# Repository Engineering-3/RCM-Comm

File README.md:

RCM-Comm
========================

This is an interface board that brings wireless communication to the RCM Control Stack. The RCM-Comm accepts the [Lantronix XPico WiFi Embedded Device Server](https://www.lantronix.com/wp-content/uploads/pdf/xPico-Wi-Fi_UG.pdf). Please see [Engineering3](http://engineering3.org/) for more information on the complete RCM Control Stack project.

Repository Contents
-------------------

* **/RCM-Comm_v1** Eagle schematic/board files, BOM, gerbers

Version History
---------------
* [RCM-Comm_v1](https://github.com/Engineering-3/RCM-Comm/tree/master/RCM-Comm_v1) - First public version - version 1 

License Information
-------------------
Hardware is released under [Solderpad Hardware License v0.51](http://solderpad.org/licenses/SHL-0.51/).
Distributed as-is; no warranty is given.

Getting Started Help
--------------------
This is a Plug-n-Play board.

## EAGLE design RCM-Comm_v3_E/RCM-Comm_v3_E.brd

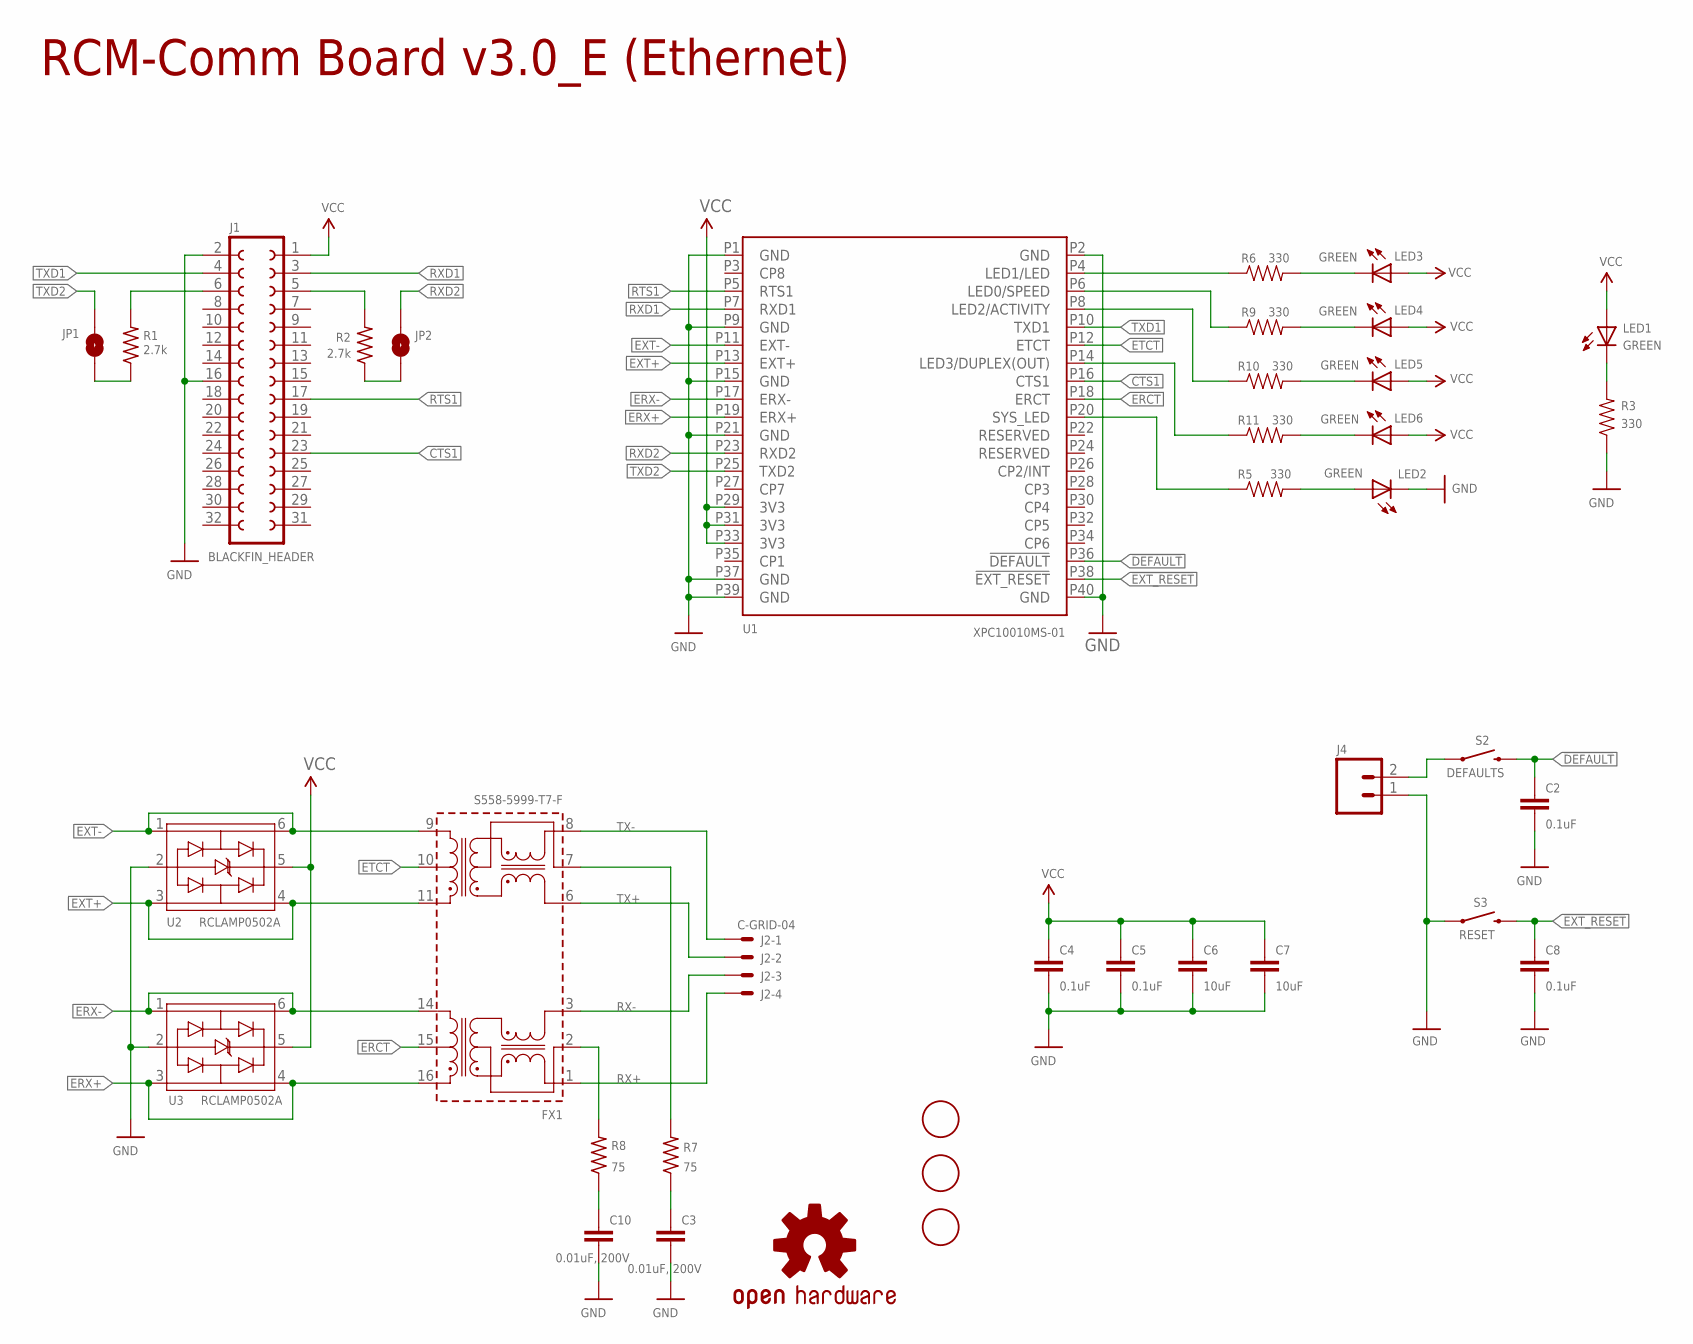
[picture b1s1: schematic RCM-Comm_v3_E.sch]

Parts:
C2, C4, C5, C8: 0.1uF; 0603-CAP
C3, C10: 0.01uF, 200V; 0603-CAP
C6, C7: 10uF; 0603-CAP
FID1, FID2, FID3: FIDUCIAL; FIDUCIAL_1MM
FX1: S558-5999-T7-F; N5
J1: BLACKFIN_HEADER; 2X16
J2-: C-GRID-04; 70555-04
J4: M02LOCK; 1X02_LOCK
JP1, JP2: JUMPER-PAD-2-NOROUND; PAD-JUMPER-2-NO_YES_SILK_ROUND
LED1, LED2, LED3, LED4, LED5, LED6: GREEN; LED-0603
LOGO1: OSHW-LOGOM; OSHW-LOGO-M
R1, R2: 2.7k; R0603
R3, R5, R6, R9, R10, R11: 330; 0603-RES
R7, R8: 75; R0603
S2: DEFAULTS; TACTILE-SWITCH-SMD
S3: RESET; TACTILE-SWITCH-SMD
U1: XPC10010MS-01; LANTRONIX_XPICO
U2, U3: RCLAMP0502A; SC-89
U$3: ROHS_GARBAGE; ROHS_GARBAGE_5MM

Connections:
!DEFAULT!: C2.1, S2.3 (2), U1.P36 (!DEFAULT!)
!EXT_RESET!: C8.1, S3.3 (2), U1.P38 (!EXT_RESET!)
CTS1: J1.23 (GP6), U1.P16 (CTS1)
ERCT: FX1.15, U1.P18 (ERCT)
ERX+: FX1.16, U1.P19 (ERX+), U3.3, U3.4
ERX-: FX1.14, U1.P17 (ERX-), U3.1, U3.6
ETCT: FX1.10, U1.P12 (ETCT)
EXT+: FX1.11, U1.P13 (EXT+), U2.3, U2.4
EXT-: FX1.9, U1.P11 (EXT-), U2.1, U2.6
GND: C2.2, C3.2, C4.2, C5.2, C6.2, C7.2, C8.2, C10.2, J1.2 (GND), J1.16 (GND16), J4.1, LED2.C, R3.1, S3.1, U1.P1 (GND), U1.P2 (GND), U1.P9 (GND), U1.P15 (GND), U1.P21 (GND), U1.P37 (GND), U1.P39 (GND), U1.P40 (GND), U2.2, U3.2
LED0_SPEED: R9.1, U1.P6 (LED0/SPEED)
LED1_LINK: R6.1, U1.P4 (LED1/LED)
LED2_ACTIVITY: R10.1, U1.P8 (LED2/ACTIVITY)
LED3_DUPLEX: R11.1, U1.P14 (LED3/DUPLEX(OUT))
unnamed: J4.2, S2.1
unnamed: JP1.2, R1.1
unnamed: LED1.C, R3.2
unnamed: JP2.1, R2.1
unnamed: LED2.A, R5.2
unnamed: FX1.2, R8.2
unnamed: LED3.C, R6.2
unnamed: C10.1, R8.1
unnamed: C3.1, R7.1
unnamed: FX1.7, R7.2
unnamed: LED6.C, R11.2
unnamed: LED5.C, R10.2
unnamed: LED4.C, R9.2
RTS1: J1.17 (GP0), U1.P5 (RTS1)
RX+: FX1.1, J2-.4
RX-: FX1.3, J2-.3
RXD1: J1.3 (TX0), U1.P7 (RXD1)
RXD2: JP2.2, U1.P23 (RXD2)
RXD2_J1: J1.5 (TX1), R2.2
SYSTEM_LED: R5.1, U1.P20 (SYS_LED)
TX+: FX1.6, J2-.2
TX-: FX1.8, J2-.1
TXD1: J1.4 (RX0), U1.P10 (TXD1)
TXD2: JP1.1, U1.P25 (TXD2)
TXD2_J1: J1.6 (RX1), R1.2
VCC: C4.1, C5.1, C6.1, C7.1, J1.1 (3.3V), LED1.A, LED3.A, LED4.A, LED5.A, LED6.A, U1.P29 (3V3), U1.P31 (3V3), U1.P33 (3V3), U2.5, U3.5

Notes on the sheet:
RCM-Comm Board v3.0_E (Ethernet)

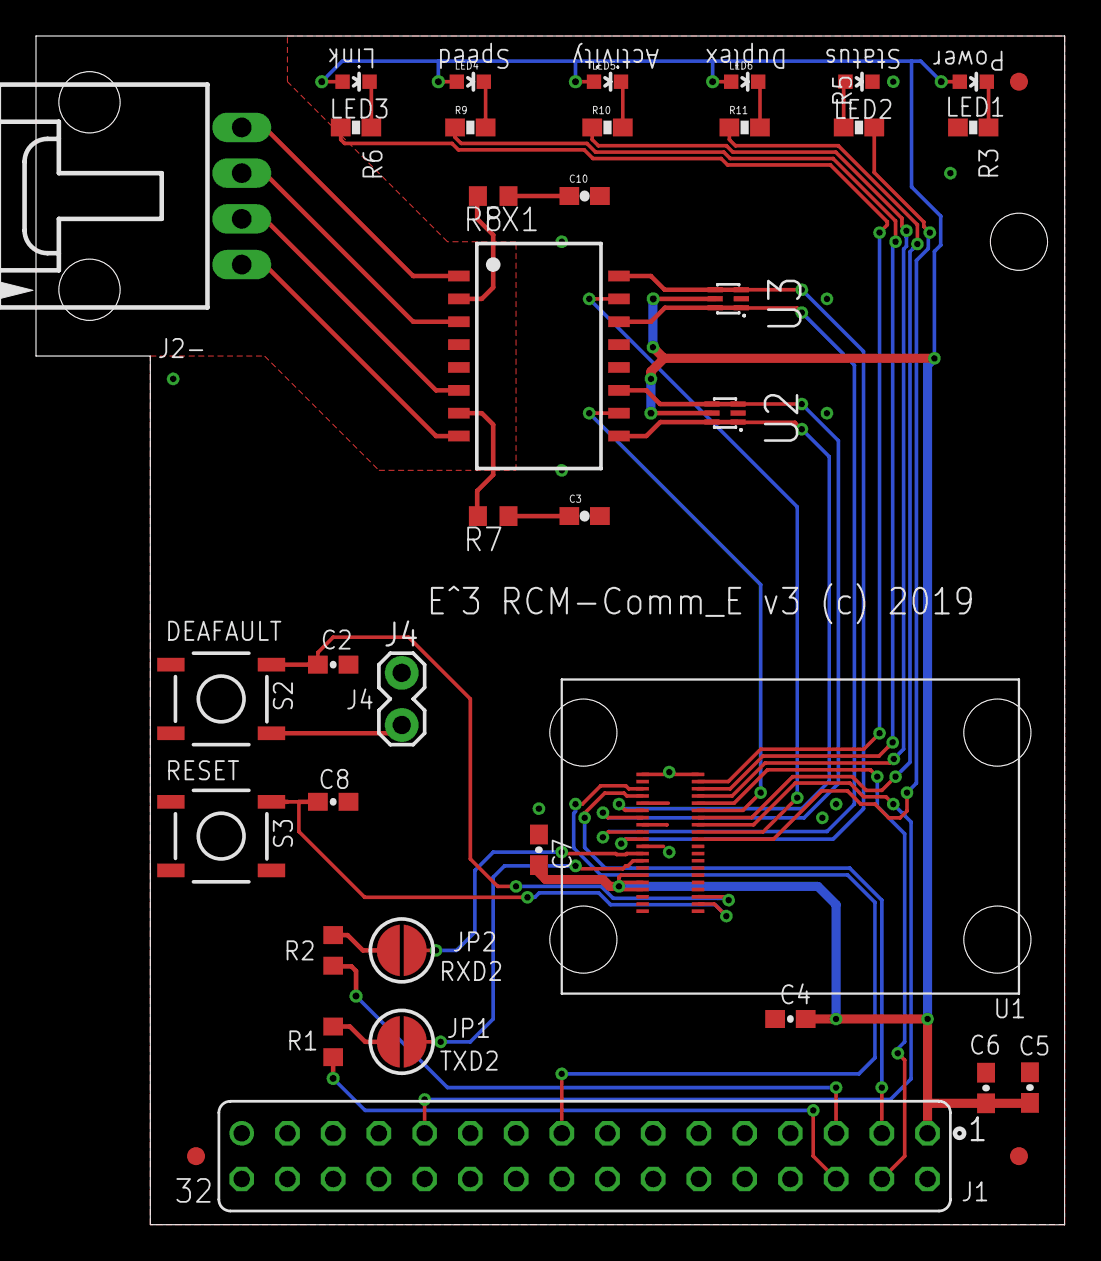
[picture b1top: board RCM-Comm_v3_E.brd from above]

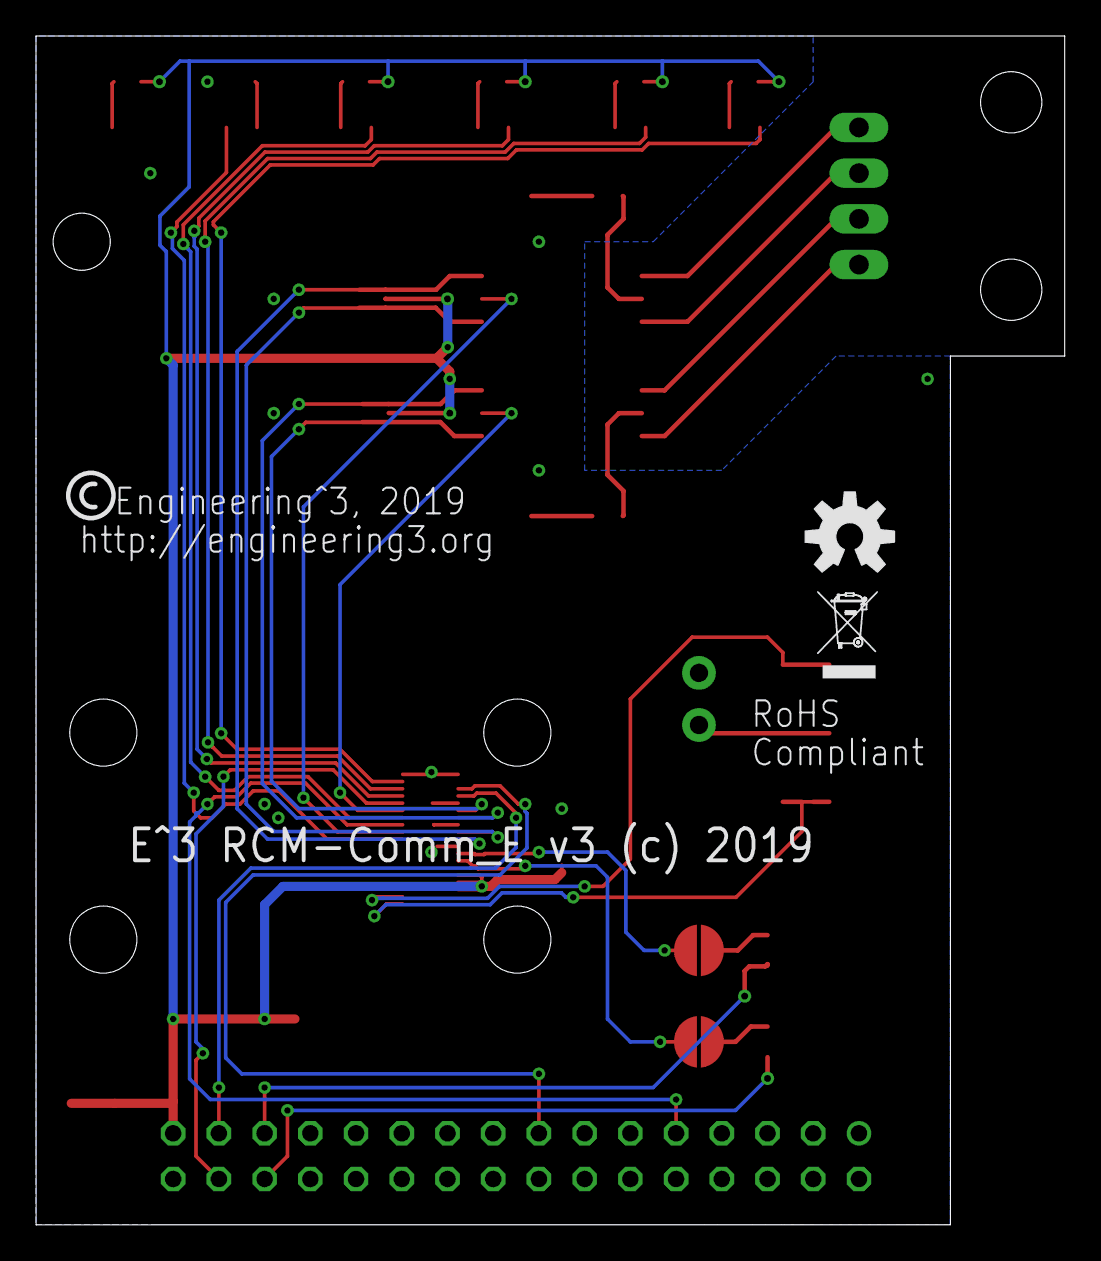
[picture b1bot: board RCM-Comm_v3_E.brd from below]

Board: 2 copper layers, 57.2 x 66.0 mm, 40 parts (2 on the bottom side), 40 nets.

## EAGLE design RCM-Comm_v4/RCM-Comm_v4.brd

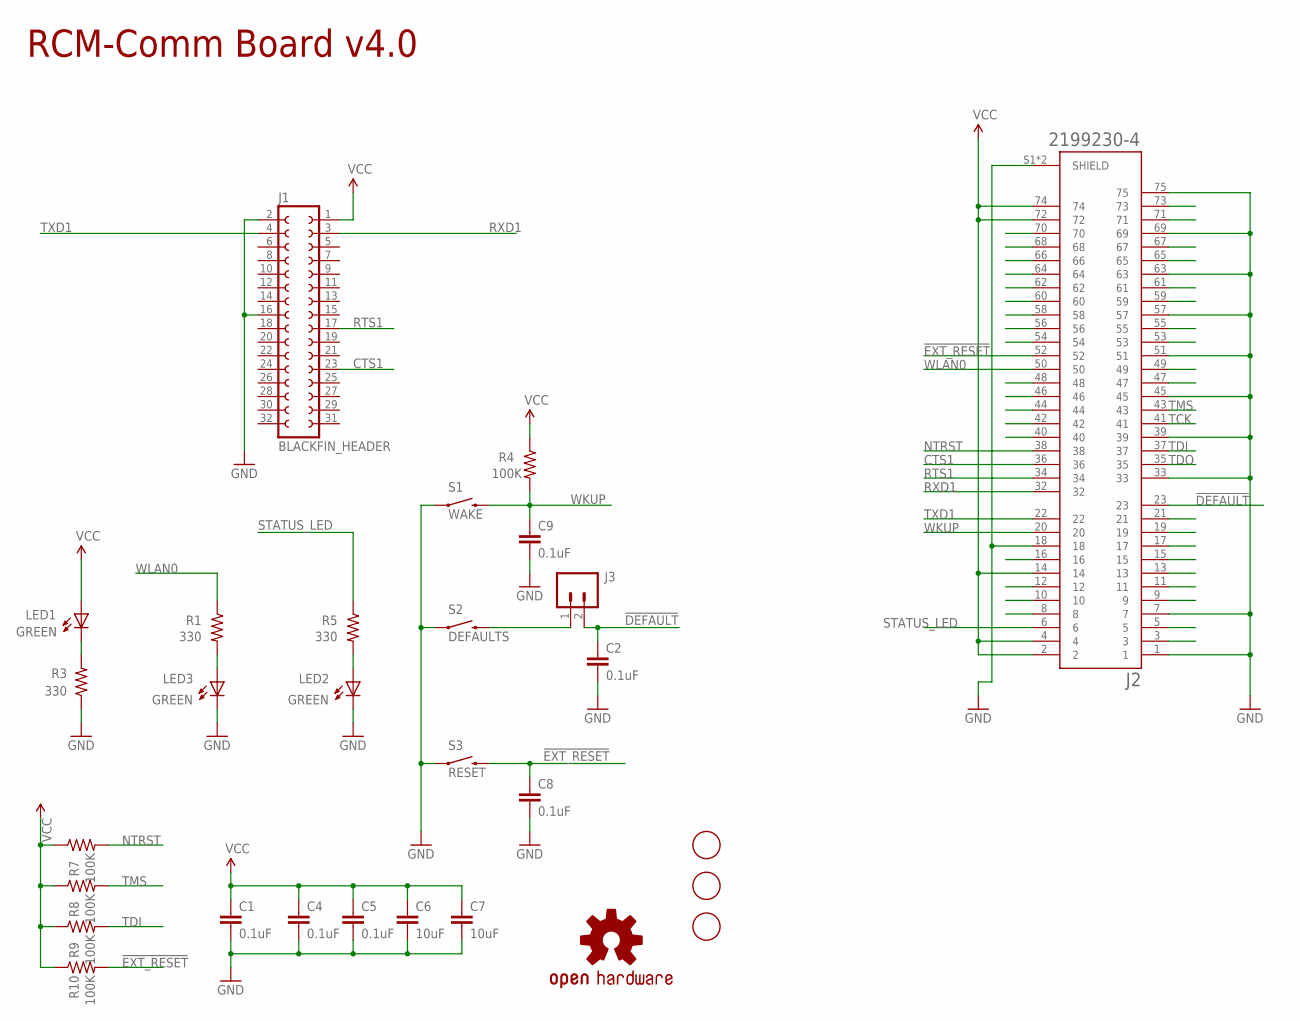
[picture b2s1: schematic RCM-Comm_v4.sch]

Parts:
C1, C2, C4, C5, C8, C9: 0.1uF; 0603-CAP
C6, C7: 10uF; 0603-CAP
FID1, FID2, FID3: FIDUCIAL; FIDUCIAL_1MM
J1: BLACKFIN_HEADER; 2X16
J2: 2199230-4; TE_2199230-4
J3: CONN_02; 1X02
LED1, LED2, LED3: GREEN; LED-0603
LOGO1: OSHW-LOGOM; OSHW-LOGO-M
R1, R3, R5: 330; 0603-RES
R4, R7, R8, R9, R10: 100K; 0603-RES
S1: WAKE; TACTILE-SWITCH-SMD
S2: DEFAULTS; TACTILE-SWITCH-SMD
S3: RESET; TACTILE-SWITCH-SMD
U$3: ROHS_GARBAGE; ROHS_GARBAGE_5MM

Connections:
!DEFAULT!: C2.1, J2.23, J3.2
!EXT_RESET!: C8.1, J2.52, R10.2, S3.3 (2)
CTS1: J1.23 (GP6), J2.36
GND: C1.2, C2.2, C4.2, C5.2, C6.2, C7.2, C8.2, C9.2, J1.2 (GND), J1.16 (GND16), J2.1, J2.7, J2.18, J2.33, J2.39, J2.45, J2.51, J2.57, J2.63, J2.69, J2.75, J2.S1 (SHIELD), J2.S2 (SHIELD), LED2.C, LED3.C, R3.1, S1.1, S2.1, S3.1
unnamed: J3.1, S2.3 (2)
unnamed: LED3.A, R1.2
unnamed: LED1.C, R3.2
unnamed: LED2.A, R5.2
NTRST: J2.38, R7.2
RTS1: J1.17 (GP0), J2.34
RXD1: J1.3 (TX0), J2.32
STATUS_LED: J2.6, R5.1
TCK: J2.41
TDI: J2.37, R9.2
TDO: J2.35
TMS: J2.43, R8.2
TXD1: J1.4 (RX0), J2.22
VCC: C1.1, C4.1, C5.1, C6.1, C7.1, J1.1 (3.3V), J2.2, J2.4, J2.14, J2.72, J2.74, LED1.A, R4.1, R7.1, R8.1, R9.1, R10.1
WKUP: C9.1, J2.20, R4.2, S1.3 (2)
WLAN0: J2.50, R1.1

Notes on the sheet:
RCM-Comm Board v4.0

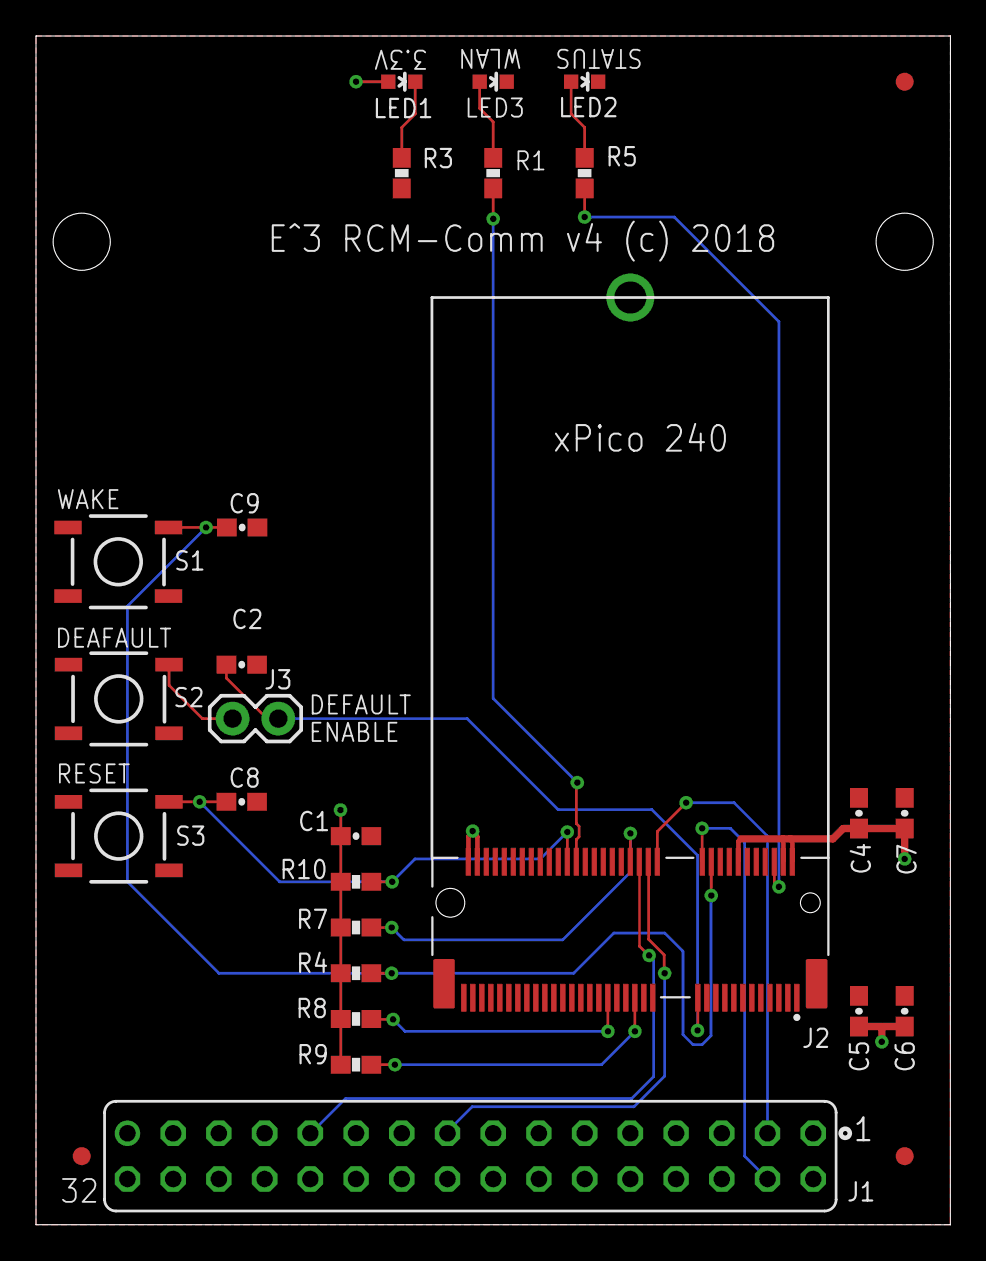
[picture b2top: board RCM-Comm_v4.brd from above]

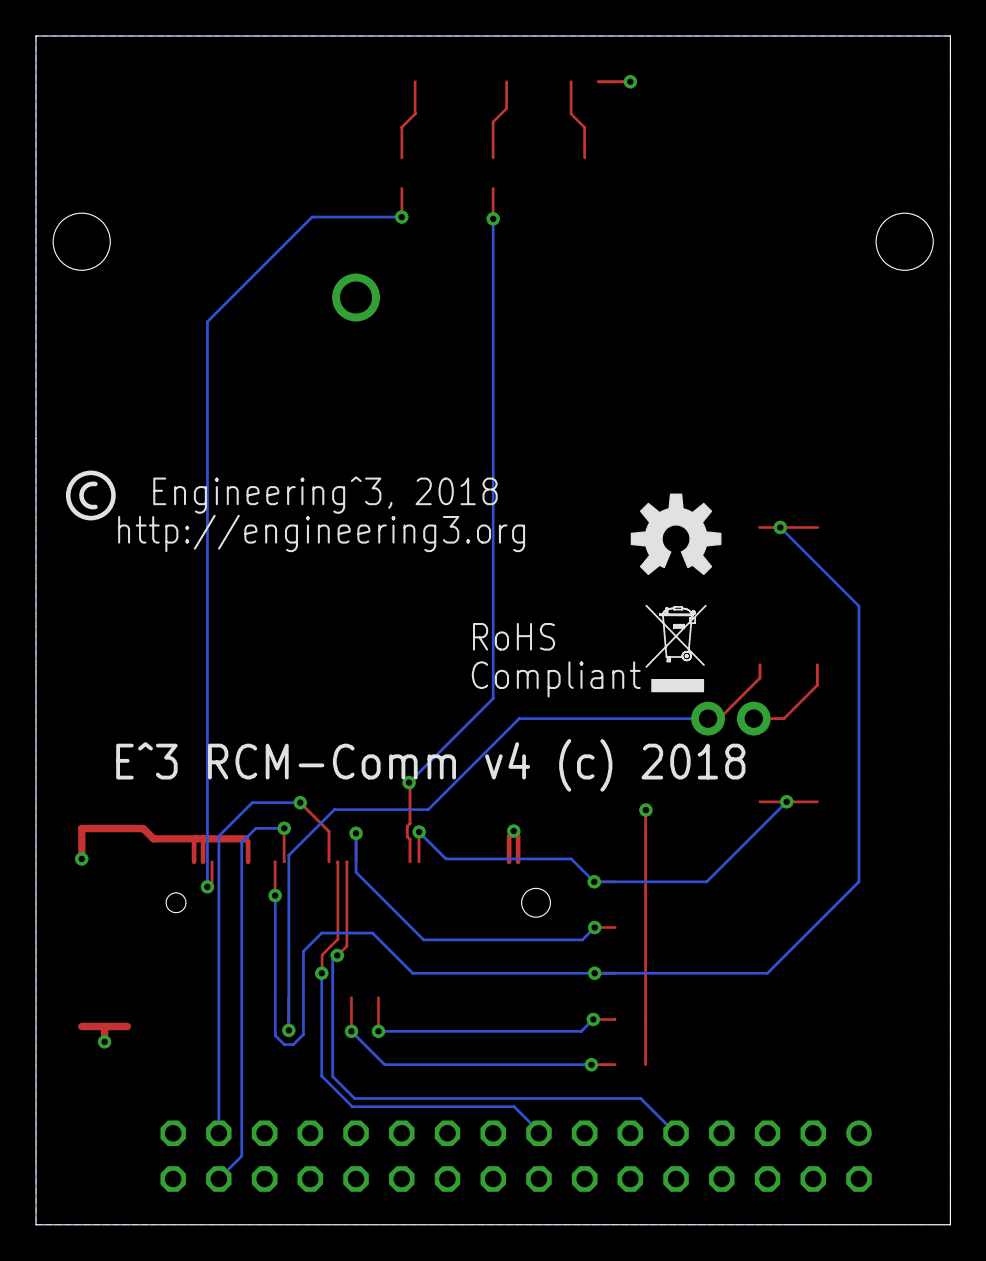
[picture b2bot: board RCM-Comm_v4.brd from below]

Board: 2 copper layers, 50.8 x 66.0 mm, 30 parts (2 on the bottom side), 18 nets.

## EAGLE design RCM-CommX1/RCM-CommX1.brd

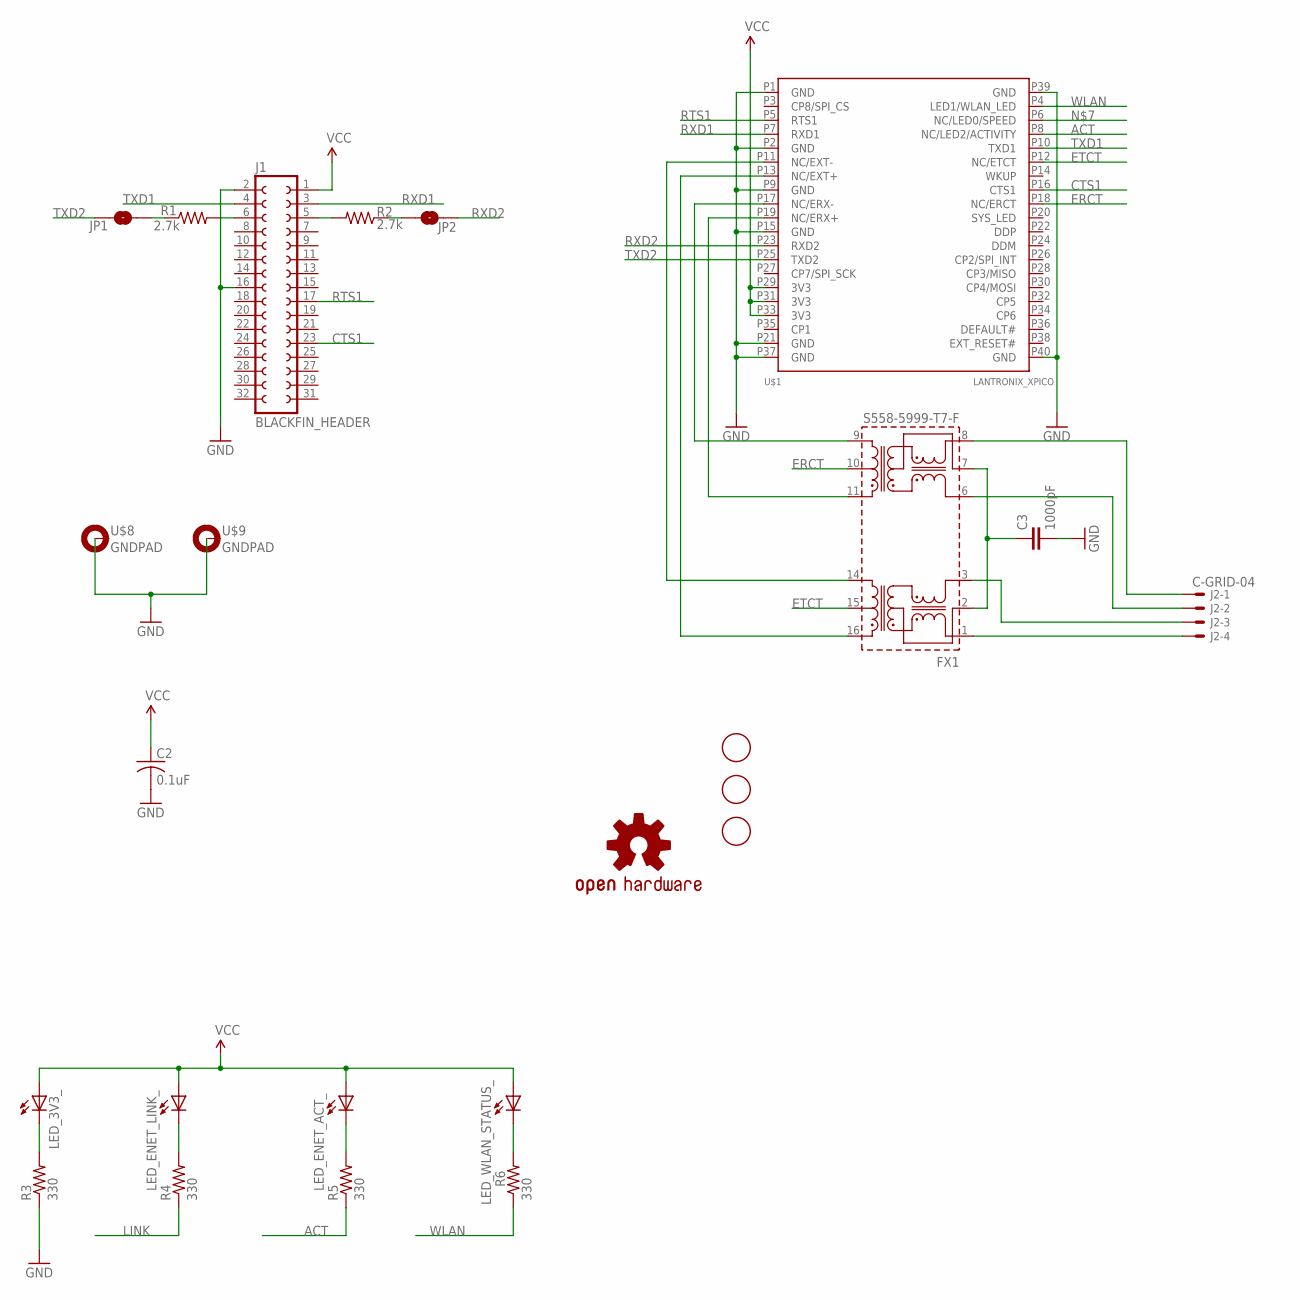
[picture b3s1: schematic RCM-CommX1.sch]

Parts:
C2: 0.1uF; C0603
C3: 1000pF; 0603-CAP
FID1, FID2, FID3: FIDUCIAL; FIDUCIAL_1MM
FX1: S558-5999-T7-F; N5
J1: BLACKFIN_HEADER; 2X16
J2-: C-GRID-04; 70555-04
JP1, JP2: JUMPER-PAD-2-NOROUND; PAD-JUMPER-2-NO_YES_SILK_ROUND
LED_3V3_: LED0603; LED-0603
LED_ENET_ACT_: LED0603; LED-0603
LED_ENET_LINK_: LED0603; LED-0603
LED_WLAN_STATUS_: LED0603; LED-0603
LOGO1: OSHW-LOGOM; OSHW-LOGO-M
R1, R2: 2.7k; R0603
R3, R4, R5, R6: 330; 0603-RES
U$1: LANTRONIX_XPICO
U$3: ROHS_GARBAGE; ROHS_GARBAGE_5MM
U$8, U$9: GNDPAD

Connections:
ACT: R5.1, U$1.P8 (NC/LED2/ACTIVITY)
CTS1: J1.23 (GP6), U$1.P16 (CTS1)
ERCT: FX1.10, U$1.P18 (NC/ERCT)
ETCT: FX1.15, U$1.P12 (NC/ETCT)
GND: C2.2, C3.2, J1.2 (GND), J1.16 (GND16), R3.1, U$1.P1 (GND), U$1.P2 (GND), U$1.P9 (GND), U$1.P15 (GND), U$1.P21 (GND), U$1.P37 (GND), U$1.P39 (GND), U$1.P40 (GND), U$8.P$1, U$9.P$1
LINK: R4.1
unnamed: C3.1, FX1.2, FX1.7
unnamed: JP1.2, R1.1
unnamed: LED_3V3_.C, R3.2
unnamed: JP2.1, R2.1
unnamed: LED_ENET_LINK_.C, R4.2
unnamed: LED_ENET_ACT_.C, R5.2
unnamed: LED_WLAN_STATUS_.C, R6.2
unnamed: FX1.16, U$1.P13 (NC/EXT+)
unnamed: FX1.14, U$1.P11 (NC/EXT-)
unnamed: FX1.11, U$1.P19 (NC/ERX+)
unnamed: FX1.9, U$1.P17 (NC/ERX-)
unnamed: FX1.1, J2-.4
unnamed: FX1.3, J2-.3
unnamed: FX1.8, J2-.1
unnamed: FX1.6, J2-.2
unnamed: J1.6 (RX1), R1.2
unnamed: J1.5 (TX1), R2.2
RTS1: J1.17 (GP0), U$1.P5 (RTS1)
RXD1: J1.3 (TX0), U$1.P7 (RXD1)
RXD2: JP2.2, U$1.P23 (RXD2)
TXD1: J1.4 (RX0), U$1.P10 (TXD1)
TXD2: JP1.1, U$1.P25 (TXD2)
VCC: C2.1, J1.1 (3.3V), LED_3V3_.A, LED_ENET_ACT_.A, LED_ENET_LINK_.A, LED_WLAN_STATUS_.A, U$1.P29 (3V3), U$1.P31 (3V3), U$1.P33 (3V3)
WLAN: R6.1, U$1.P4 (LED1/WLAN_LED)

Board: 2 copper layers, 25 parts (2 on the bottom side), 29 nets, no tracks yet.

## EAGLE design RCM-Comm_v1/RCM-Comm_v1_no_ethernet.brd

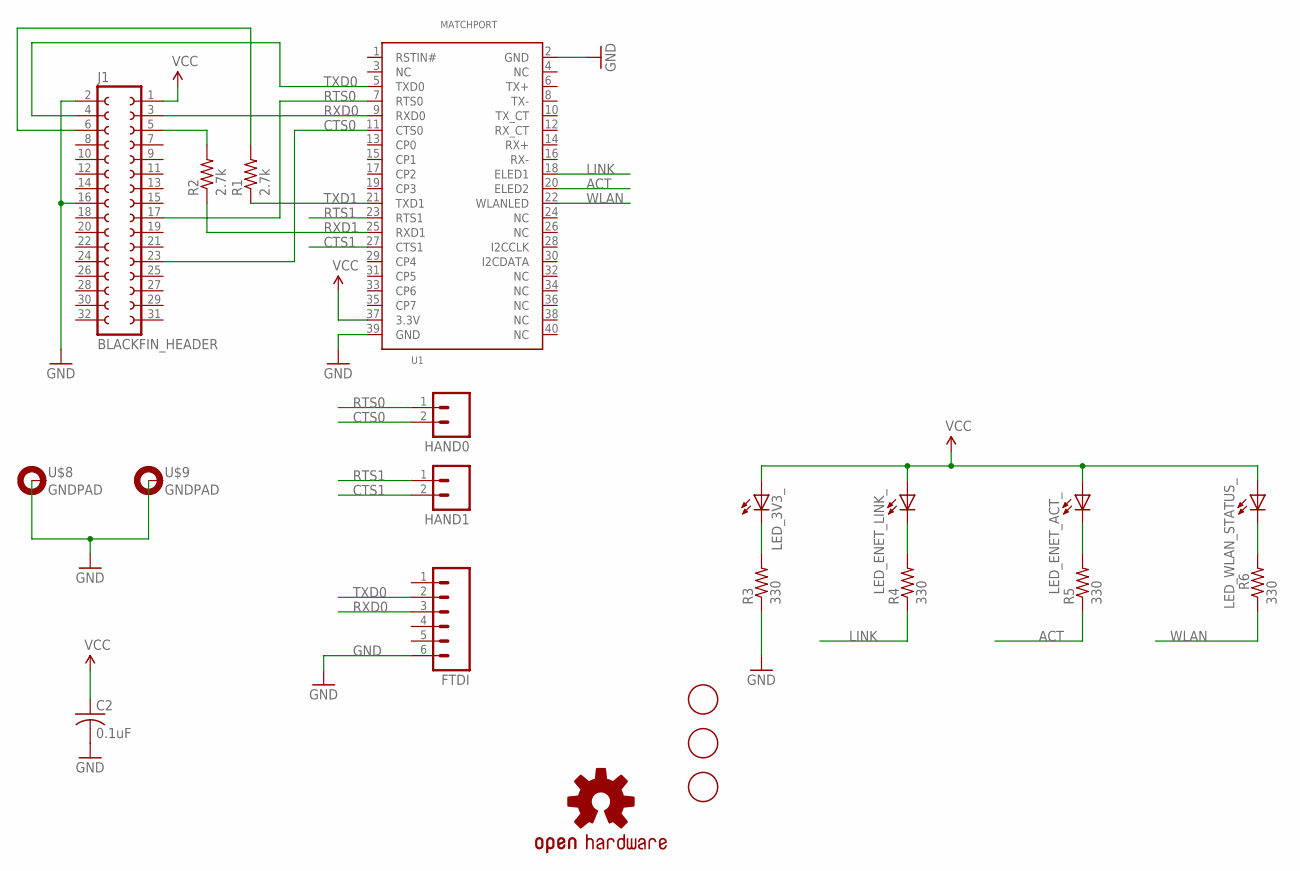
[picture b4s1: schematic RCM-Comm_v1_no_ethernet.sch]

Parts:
C2: 0.1uF; C0603
FID1, FID2, FID3: FIDUCIAL; FIDUCIAL_1MM
FTDI: M06SIP; 1X06
HAND0, HAND1: M02PTH; 1X02
J1: BLACKFIN_HEADER; 2X16
LED_3V3_: LED0603; LED-0603
LED_ENET_ACT_: LED0603; LED-0603
LED_ENET_LINK_: LED0603; LED-0603
LED_WLAN_STATUS_: LED0603; LED-0603
LOGO1: OSHW-LOGOM; OSHW-LOGO-M
R1, R2: 2.7k; 0207/10
R3, R4, R5, R6: 330; 0603-RES
U1: MATCHPORT; MATCHPORT_LAYOUT
U$3: ROHS_GARBAGE; ROHS_GARBAGE_5MM
U$8, U$9: GNDPAD

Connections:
ACT: R5.1, U1.20 (ELED2)
CTS0: HAND0.2, J1.23 (GP6), U1.11 (CTS0)
CTS1: HAND1.2, U1.27 (CTS1)
GND: C2.2, FTDI.6, J1.2 (GND), J1.16 (GND16), R3.1, U1.2 (GND), U1.39 (GND), U$8.P$1, U$9.P$1
LINK: R4.1, U1.18 (ELED1)
unnamed: LED_3V3_.C, R3.2
unnamed: LED_ENET_LINK_.C, R4.2
unnamed: LED_ENET_ACT_.C, R5.2
unnamed: LED_WLAN_STATUS_.C, R6.2
unnamed: J1.6 (RX1), R1.2
unnamed: J1.5 (TX1), R2.2
RTS0: HAND0.1, J1.17 (GP0), U1.7 (RTS0)
RTS1: HAND1.1, U1.23 (RTS1)
RXD0: FTDI.3, J1.3 (TX0), U1.9 (RXD0)
RXD1: R2.1, U1.25 (RXD1)
TXD0: FTDI.2, J1.4 (RX0), U1.5 (TXD0)
TXD1: R1.1, U1.21 (TXD1)
VCC: C2.1, J1.1 (3.3V), LED_3V3_.A, LED_ENET_ACT_.A, LED_ENET_LINK_.A, LED_WLAN_STATUS_.A, U1.37 (3.3V)
WLAN: R6.1, U1.22 (WLANLED)

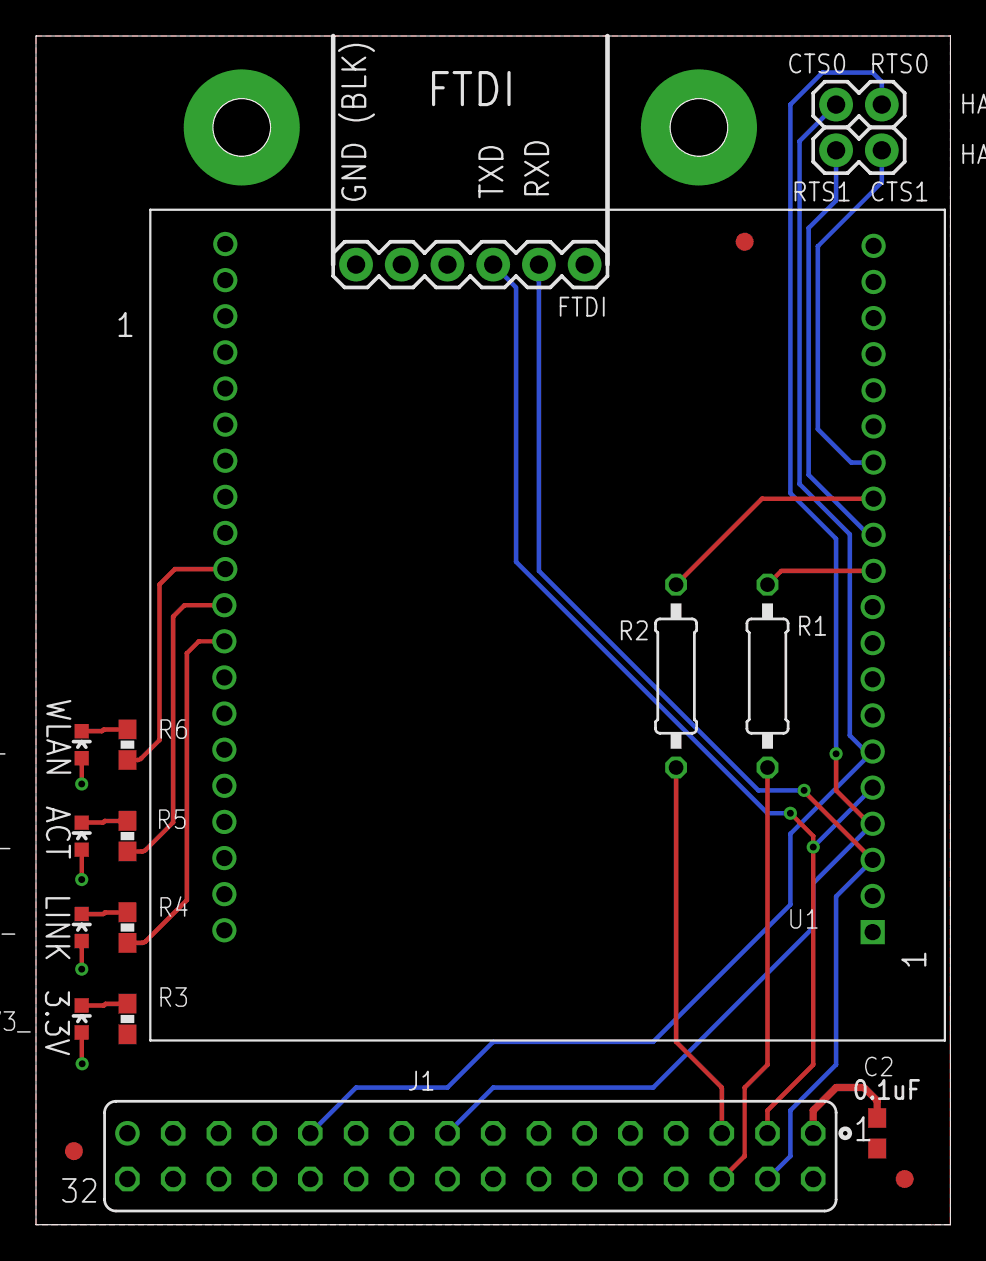
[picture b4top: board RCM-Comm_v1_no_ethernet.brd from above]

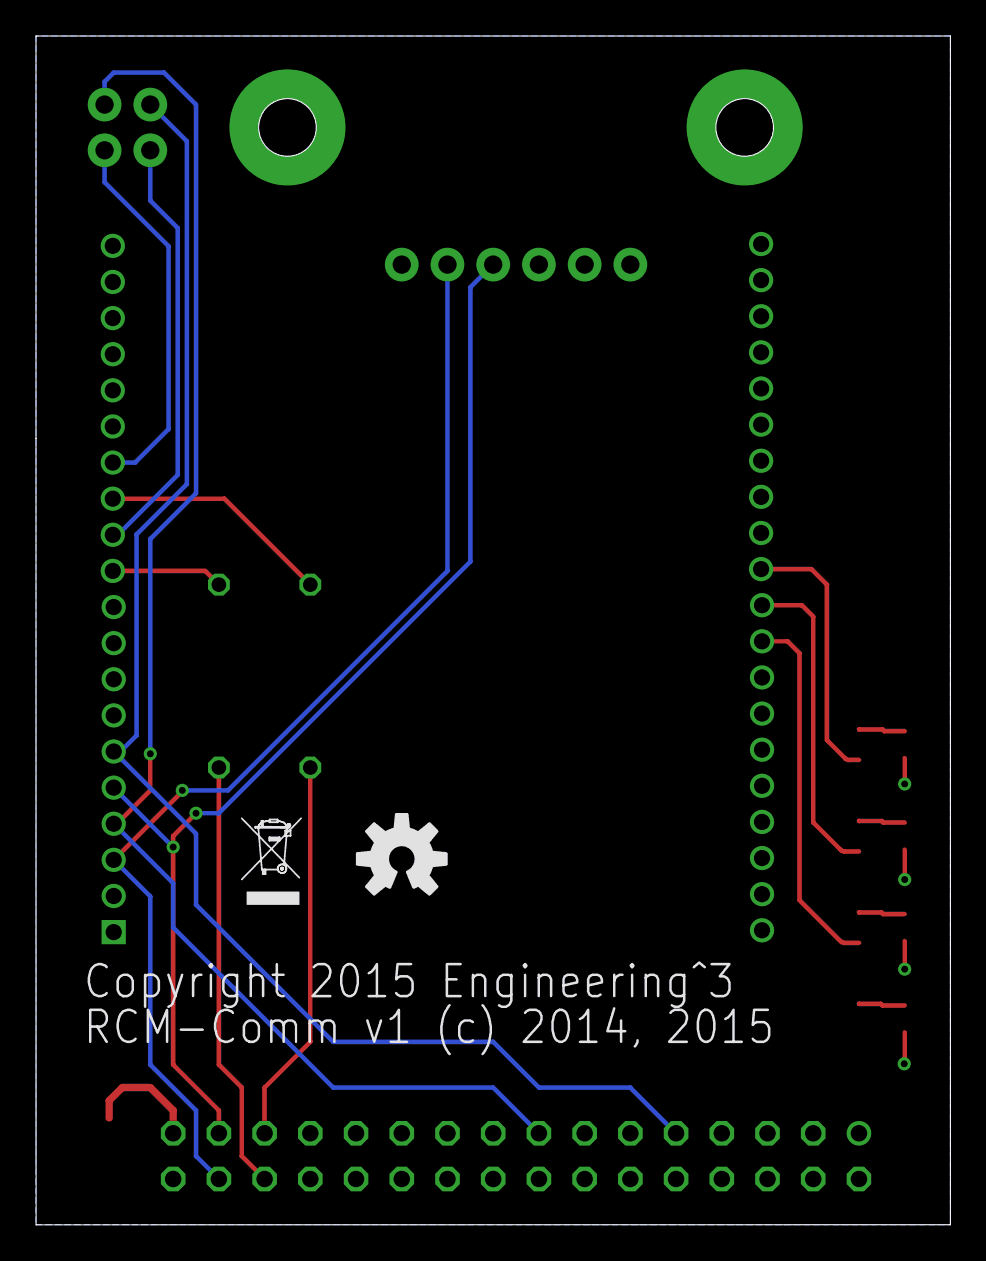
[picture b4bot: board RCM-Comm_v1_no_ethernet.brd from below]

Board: 2 copper layers, 50.8 x 66.0 mm, 23 parts (2 on the bottom side), 19 nets.

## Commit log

2015-02-14 Initial checkin of files from Logic.
2015-02-16 Updated file names and added details to board and schematic.
2015-02-19 Added readme.
2015-11-02 New version of board without Ethernet connector (and thus a true rectangle shape.)
2016-01-24 Started xPico version of RCM-Comm board.
2016-02-05 Version 2.0 of RCM-Comm board ready for review.
2016-02-05 Folder name change.
2016-02-05 Fixed attribution text in schematic.
2016-02-06 Updated BOM for v2 of board.
2016-03-10 Added text to back silk.
2016-03-10 Renaming to _W
2016-03-10 Renaming to add _W
2016-03-14 Updated 2x16 connector with new part number (reduces space between BFin and Comm board)
2016-05-30 V3 of the RCM-Comm Board * Moved mounting holes
2016-08-01 Adding board build readme.
2016-08-18 Updated positions of component reference designators on the board, and created pdf of board file
2018-10-22 Added note about next radio version
2018-12-23 RCM-COmm_v4 (a) design complete. Gerbers ready for fab pending approval.
2018-12-24 Added DEFAULT ENABLE header back in, re-rendered top and bottom for approval.
2018-12-29 Added WLAN Led on configurable pin (CP) #1.
2018-12-31 Fixed silk screen text on bottom of board (removed "W")
2019-01-02 Started BOM
2019-01-02 Updated final BOM. Final 'd' version of gerbers, which got sent to JLCPCB.
2019-03-16 Starting work on RCM-Comm_v3_E (Ethernet)
2019-03-16 Got Ethernet version of RCM-Comm_v3 board pretty much done. Out for Tim's review.
2019-10-06 Added relevant datasheets.

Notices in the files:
RCM-CommX1/RCM-CommX1.brd:
Copyright 2015 Engineering^3
RCM-Comm v1 (c) 2014, 2015
RCM-CommX1/RCM-CommX1.sch:
Copyright 2016 Engineering^3 LLC
Copyright 2016 Engineering^3 LLC Copyright and related rights are licensed under the Solderpad Hardware License,
Version 0.51 (the “License”); you may not use this file except in compliance with the License. You may obtain a copy
RCM-Comm_v1/RCM-Comm_v1_no_ethernet.sch:
Copyright 2015 Engineering^3 LLC
Copyright 2015 Engineering^3 LLC Copyright and related rights are licensed under the Solderpad Hardware License,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
